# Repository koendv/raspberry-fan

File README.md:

# LTC1695 Raspberry Fan Controller

This is a fan speed controller for the Raspberry Pi. There is a smaller, cheaper version of the same controller [here](https://github.com/koendv/minimal_raspberry_fan).

## Hat

If you look at the [schematic](doc/schematic.pdf) you'll see the *hat* contains only two ic's: U1, an LTC1695 fan controller, and U2, a 24c32 EEPROM. The data in the EEPROM allows Raspbian to identify the hat. If you are making this for yourself, you can safely leave the EEPROM out.  That leaves us with the following components: 

Quant.|Item
---|--
1|LTC1695CS5  I2C Fan Speed Controller, SOT-23
2|KEMET T494B475K020AT Tantalum Capacitor, SMD 20V 4.7uF 1311 10% ESR=1 Ohms
1|Adafruit Accessories Header for Raspberry Pi
1|Sunon MF40200V3-1000U-A99 DC Fan 40mm, 5V.

The fan is 40mm, 5V DC, brushless, 2 wire, **1W max**. 
Adafruit has two GPIO headers for Raspberry, product numbers [1992](https://www.adafruit.com/product/1992) (tall, 16.5 mm) and  [2243](https://www.adafruit.com/product/2243) (short, 5.0 mm). Choose the one that clears the heatsink of the processor. 
## Installation
Enable i2c bus 1 clicking on the raspberry icon -> Preferences -> Raspberry Pi Configuration -> Interfaces -> i2c.
If you scan the i2c bus, you ought to see the fan controller at address 0x74:
```
koen@raspberrypi:~ $ sudo i2cdetect -r -y 1
     0  1  2  3  4  5  6  7  8  9  a  b  c  d  e  f
00:          -- -- -- -- -- -- -- -- -- -- -- -- -- 
10: -- -- -- -- -- -- -- -- -- -- -- -- -- -- -- -- 
20: -- -- -- -- -- -- -- -- -- -- -- -- -- -- -- -- 
30: -- -- -- -- -- -- -- -- -- -- -- -- -- -- -- -- 
40: -- -- -- -- -- -- -- -- -- -- -- -- -- -- -- -- 
50: -- -- -- -- -- -- -- -- -- -- -- -- -- -- -- -- 
60: -- -- -- -- -- -- -- -- -- -- -- -- -- -- -- -- 
70: -- -- -- -- 74 -- -- --                         
koen@raspberrypi:~ $ 
```
You can switch the fan completely on:
```
i2cset -y 1 0x74 63
```
completely off:
```
i2cset -y 1 0x74 0
```
or something in between:
```
i2cset -y 1 0x74 32
```
At low speeds, the fan might need a little extra push to get going. If you add 64 to the speed the fan will run at full speed for 0.25s, then slow down to the normal speed. As an example
```
i2cset -y 1 0x74 84
```
runs the  fan at the full 5V for a quarter second to get the fan moving, then drops to 1.56V for normal operation.

Lastly, you can read the fan controller status:
```
i2cget -y 1 0x74 
```

Value | Status
--------|--------
0|ok
64|thermal shutdown (T > 155 degree C)
128|overcurrent (I > 390mA)
192|thermal shutdown *and* overcurrent

## Running

The ```raspbian``` directory contains ```fanctl.py```, a python script which you can run either interactively or in the background. Feel free to modify the script as you wish. The values for *fan_min* and *fan_boost* are for the fan I'm using. The values  *temp_min* and *temp_max* represent personal choices. Once you are happy with the values, you can add the fan controller to ```/etc/rc.local``` so the fan starts up at boot:
```
/usr/local/bin/fanctl.py &
```

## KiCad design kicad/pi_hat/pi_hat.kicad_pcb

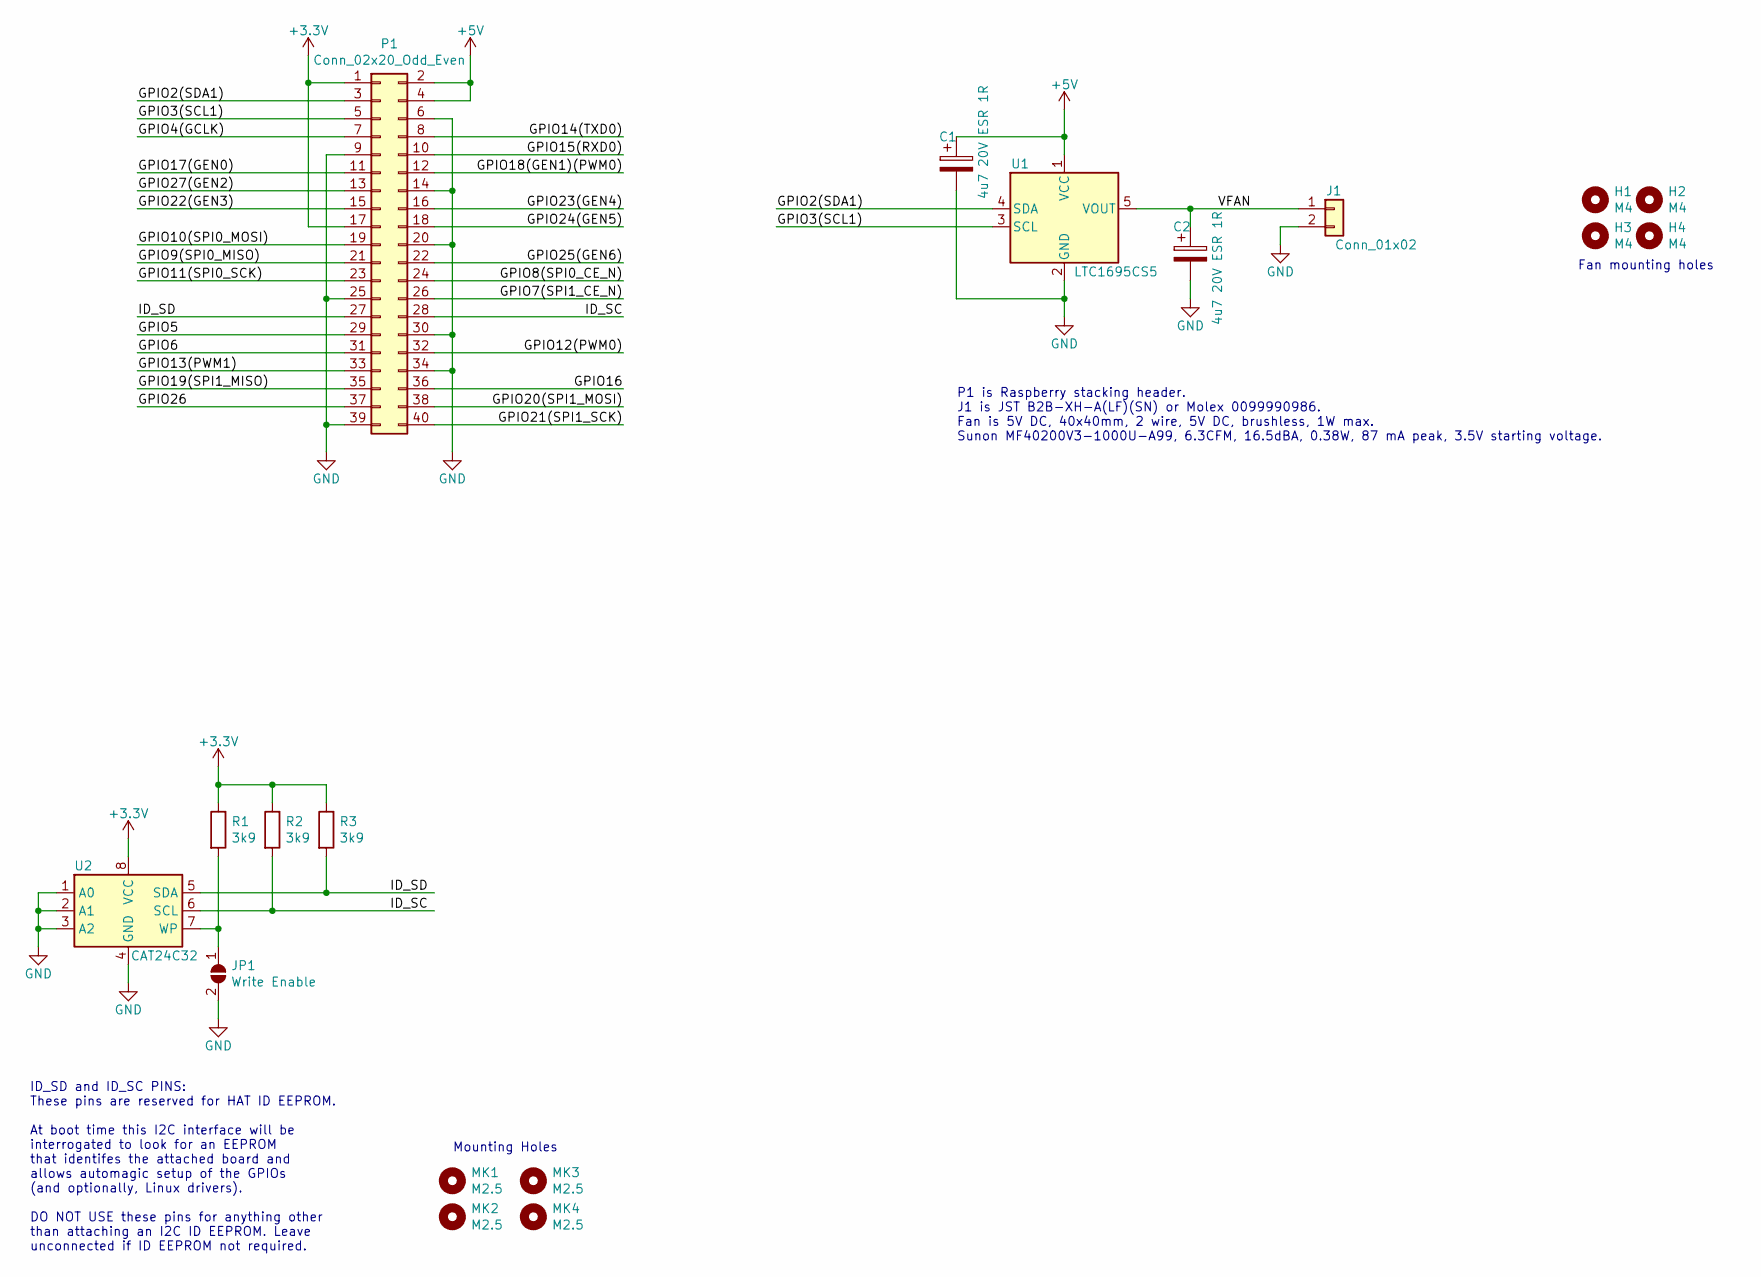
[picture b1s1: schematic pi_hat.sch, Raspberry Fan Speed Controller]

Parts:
C1, C2: 4u7 20V ESR 1R; CP_EIA-3528-12_Kemet-T
H1, H2, H3, H4: M4; MountingHole_4.3mm_M4
J1: Conn_01x02; JST_XH_B02B-XH-A_1x02_P2.50mm_Vertical
JP1: Write Enable; SolderJumper-2_P1.3mm_Open_Pad1.0x1.5mm
MK1, MK2, MK3, MK4: M2.5; MountingHole_2.7mm_M2.5
P1: Conn_02x20_Odd_Even; PinSocket_2x20_P2.54mm_Vertical
R1, R2, R3: 3k9; R_0805_2012Metric
U1: LTC1695CS5; TSOT-23-5
U2: CAT24C32; SOIC-8_3.9x4.9mm_P1.27mm

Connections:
+3V3: P1.1, P1.17, R1.1, R2.1, R3.1, U2.8 (VCC)
+5V: C1.1, P1.2, P1.4, U1.1 (VCC)
/GPIO2(SDA1): P1.3, U1.4 (SDA)
/GPIO3(SCL1): P1.5, U1.3 (SCL)
/GPIO4(GCLK): P1.7
/GPIO5: P1.29
/GPIO6: P1.31
/GPIO7(SPI1_CE_N): P1.26
/GPIO8(SPI0_CE_N): P1.24
/GPIO9(SPI0_MISO): P1.21
/GPIO10(SPI0_MOSI): P1.19
/GPIO11(SPI0_SCK): P1.23
/GPIO12(PWM0): P1.32
/GPIO13(PWM1): P1.33
/GPIO14(TXD0): P1.8
/GPIO15(RXD0): P1.10
/GPIO16: P1.36
/GPIO17(GEN0): P1.11
/GPIO18(GEN1)(PWM0): P1.12
/GPIO19(SPI1_MISO): P1.35
/GPIO20(SPI1_MOSI): P1.38
/GPIO21(SPI1_SCK): P1.40
/GPIO22(GEN3): P1.15
/GPIO23(GEN4): P1.16
/GPIO24(GEN5): P1.18
/GPIO25(GEN6): P1.22
/GPIO26: P1.37
/GPIO27(GEN2): P1.13
/ID_SC: P1.28, R2.2, U2.6 (SCL)
/ID_SD: P1.27, R3.2, U2.5 (SDA)
/VFAN: C2.1, J1.1, U1.5 (VOUT)
GND: C1.2, C2.2, J1.2, JP1.2 (B), P1.6, P1.9, P1.14, P1.20, P1.25, P1.30, P1.34, P1.39, U1.2 (GND), U2.1 (A0), U2.2 (A1), U2.3 (A2), U2.4 (GND)
unnamed: JP1.1 (A), R1.2, U2.7 (WP)

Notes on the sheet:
ID_SD and ID_SC PINS: These pins are reserved for HAT ID EEPROM. At boot time this I2C interface will be interrogated to look for an EEPROM that identifes the attached board and allows automagic setup of the GPIOs (and optionally, Linux drivers). DO NOT USE these pins for anything other than attach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
Mounting Holes
Fan mounting holes
P1 is Raspberry stacking header. J1 is JST B2B-XH-A(LF)(SN) or Molex 0099990986. Fan is 5V DC, 40x40mm, 2 wire, 5V DC, brushless, 1W max. Sunon MF40200V3-1000U-A99, 6.3CFM, 16.5dBA, 0.38W, 87 mA peak, 3.5V starting voltage.

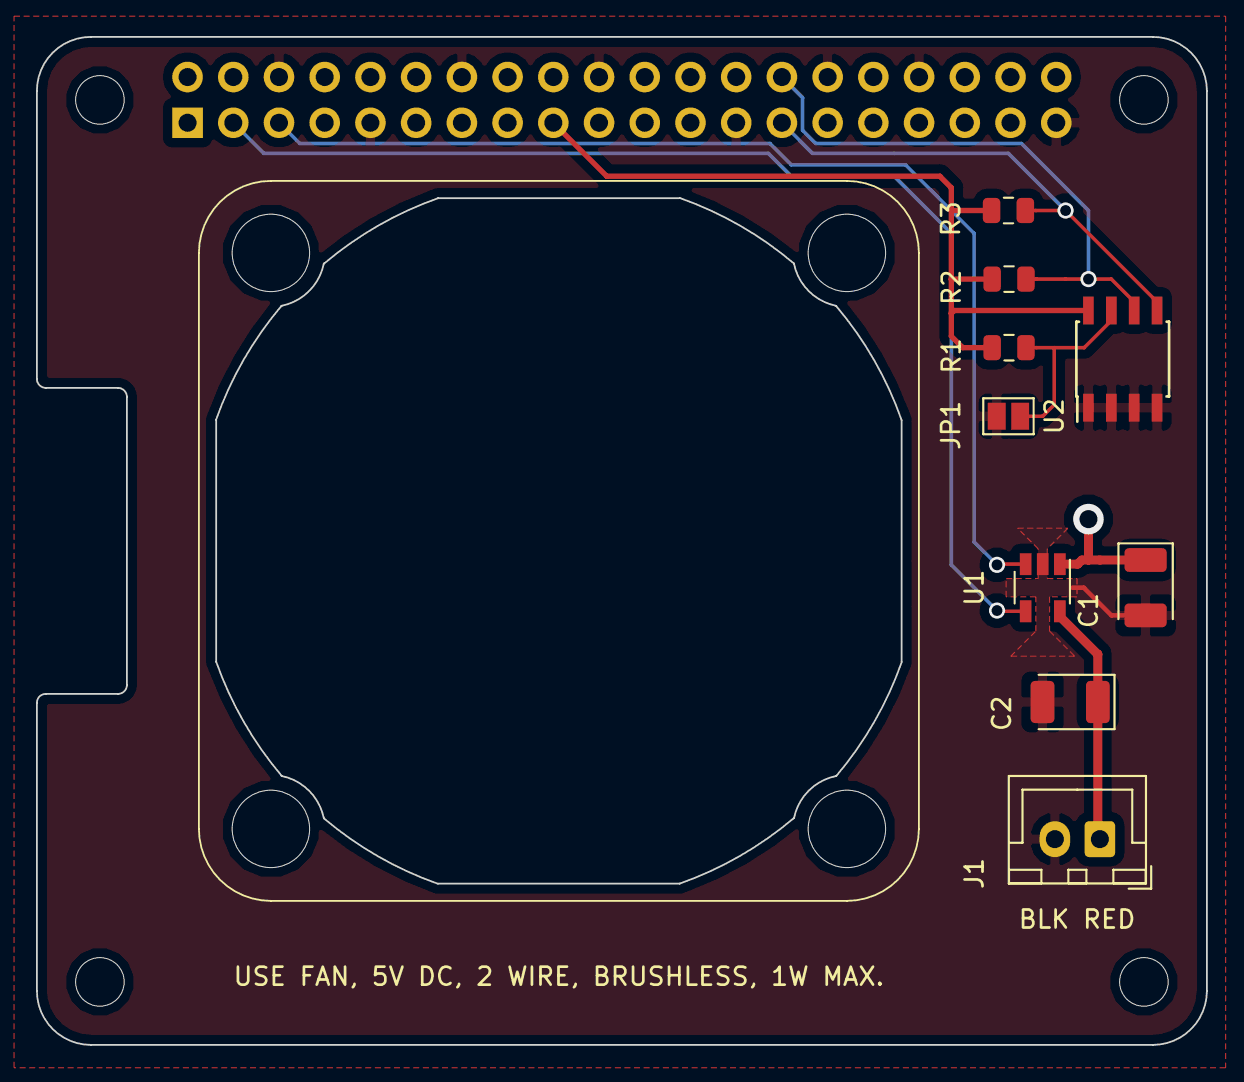
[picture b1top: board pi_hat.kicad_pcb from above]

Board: 2 copper layers, 65.0 x 56.0 mm, 18 parts (0 on the bottom side), 9 nets.

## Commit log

2019-08-26 initial version
2019-08-26 typo
2019-09-03 add temp
2019-09-04 script
2022-02-26 systemd

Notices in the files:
kicad/pi_hat/pi_hat.kicad_pcb:
Released under the Creative Commons Attribution-ShareAlike 4.0 license.
